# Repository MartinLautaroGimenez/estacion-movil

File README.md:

# Estación Meteorológica Móvil

Esta estación meteorológica móvil está equipada con una variedad de sensores y componentes para medir y registrar datos ambientales clave. Desde la presión atmosférica hasta la calidad del aire, esta estación proporciona información precisa para proyectos institucionales y aplicaciones diversas.

## Sensores y Componentes:

- **Módulo Sensor de Presión Atmosférica y Temperatura BMP180 (Arduino):** Proporciona lecturas precisas de la presión atmosférica y la temperatura.
- **Sensor DHT22 de Humedad y Temperatura (Arduino/Raspberry Pi):** Ofrece mediciones confiables de humedad y temperatura en tiempo real.
- **Arduino Nano Compatible ATmega328 USB C con Pines Soldados:** Controla y coordina el funcionamiento de los sensores y otros componentes.
- **Módulo Lector de Memorias Micro SD (Arduino):** Permite almacenar datos recopilados para análisis posterior.
- **Tarjeta Micro SD SanDisk Ultra 8GB Clase 10:** Proporciona capacidad de almacenamiento para registros de datos extensos.
- **BMS 2S 3A 8,4V para Baterías 18650 (2 celdas):** Protege y gestiona la carga de las baterías para una operación segura y eficiente.
- **Batería 18650 UltraFire HY18650 Cilíndrica:** Fuente de energía portátil para la estación meteorológica móvil.
- **LM2596 Fuente Step-Down DC-DC 1,23-35V 3A (Arduino):** Regula el voltaje de entrada para alimentar los componentes de manera estable.
- **Módulo Sensor de Luz Digital Ambiente BH1750 GY-302 (Arduino):** Detecta y registra niveles de luz ambiental.
- **Sensor MQ-135 de Gas (NH3, N2, CO2, Humo, etc.):** Monitoriza la calidad del aire para detectar la presencia de varios gases.

## Uso y Aplicaciones:

Esta estación meteorológica móvil es ideal para proyectos institucionales que requieren datos precisos y actualizados sobre condiciones ambientales. Puede utilizarse en una variedad de aplicaciones, incluyendo:

- Monitoreo ambiental en tiempo real.
- Investigación climática y meteorológica.
- Control de calidad del aire en entornos interiores y exteriores.
- Estudios de impacto ambiental y análisis de datos.

Con su diseño compacto y su capacidad de recopilación de datos precisa, esta estación meteorológica móvil es una herramienta valiosa para cualquier proyecto que requiera información ambiental detallada y confiable.

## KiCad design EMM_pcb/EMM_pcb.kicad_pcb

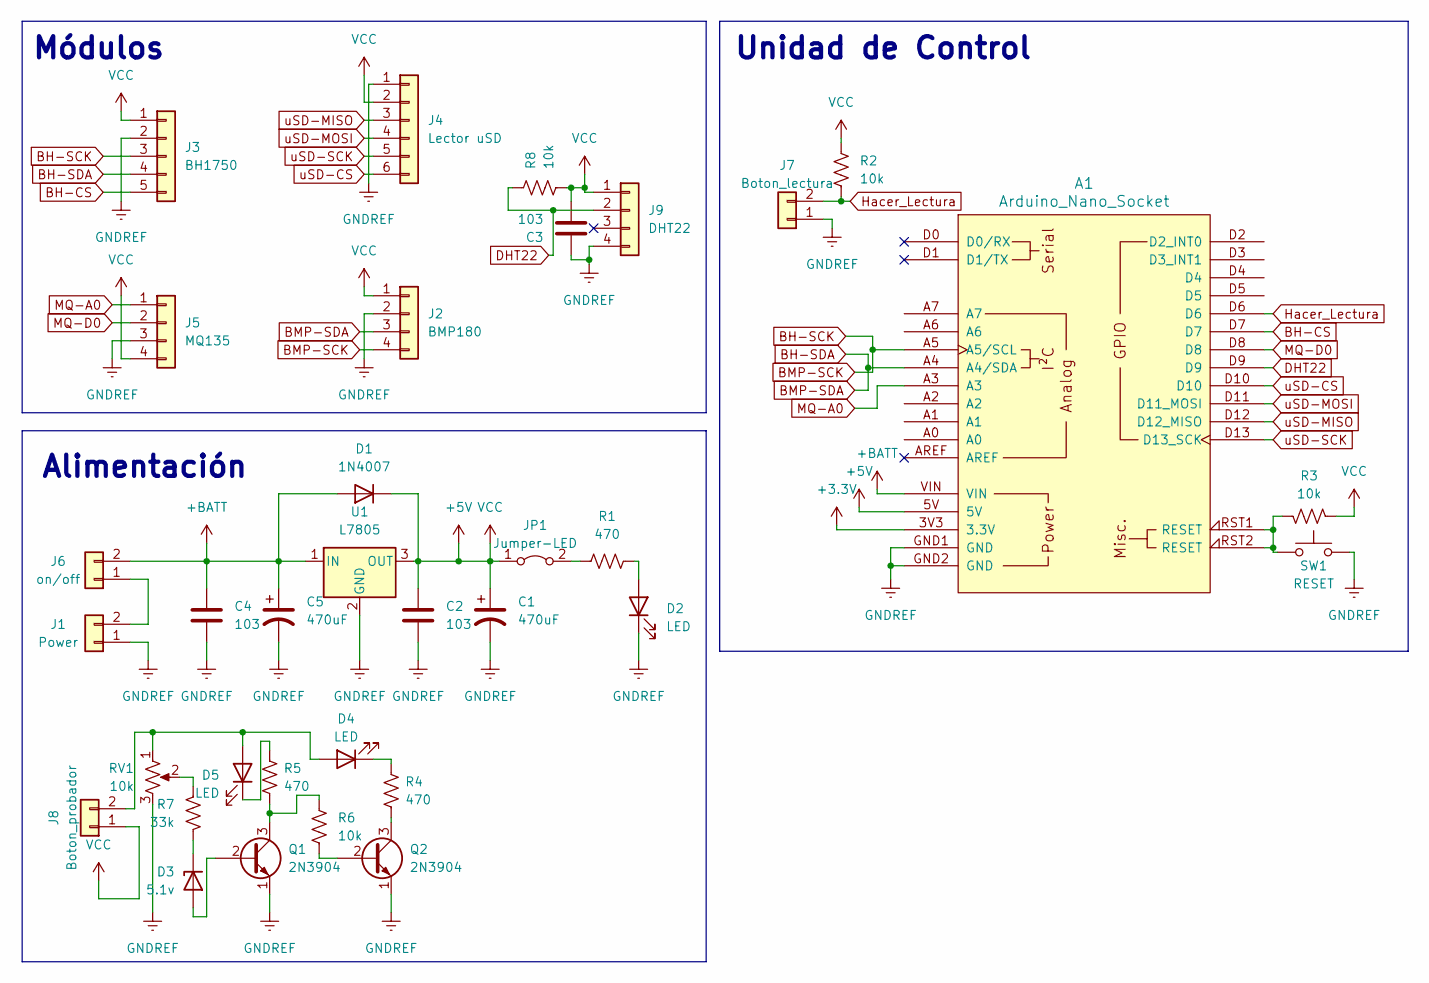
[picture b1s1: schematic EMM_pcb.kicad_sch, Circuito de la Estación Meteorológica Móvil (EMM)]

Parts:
A1: Arduino_Nano_Socket
C1, C5: 470uF; CP_Radial_D10.0mm_P5.00mm
C2, C3, C4: 103; C_Disc_D6.0mm_W2.5mm_P5.00mm
D1: 1N4007; D_DO-41_SOD81_P10.16mm_Horizontal
D2, D4, D5: LED; LED_D5.0mm
D3: 5.1v; D_DO-35_SOD27_P10.16mm_Horizontal
J1: Power; PinHeader_2x01_P2.54mm_Vertical
J2: BMP180; PinHeader_1x04_P2.54mm_Vertical
J3: BH1750; PinHeader_1x05_P2.54mm_Vertical
J4: Lector uSD; PinHeader_1x06_P2.54mm_Vertical
J5: MQ135; PinHeader_1x04_P2.54mm_Vertical
J6: on/off; PinHeader_1x02_P2.54mm_Vertical
J7: Boton_lectura; PinHeader_1x02_P2.54mm_Vertical
J8: Boton_probador; PinHeader_1x02_P2.54mm_Vertical
J9: DHT22; PinHeader_1x04_P2.54mm_Vertical
JP1: Jumper-LED; PinHeader_1x02_P2.54mm_Vertical
Q1, Q2: 2N3904; TO-92_Wide
R1, R4, R5: 470; R_Axial_DIN0207_L6.3mm_D2.5mm_P10.16mm_Horizontal
R2, R3, R6, R8: 10k; R_Axial_DIN0207_L6.3mm_D2.5mm_P10.16mm_Horizontal
R7: 33k; R_Axial_DIN0207_L6.3mm_D2.5mm_P10.16mm_Horizontal
RV1: 10k; Potentiometer_Bourns_3339P_Vertical_HandSoldering
SW1: RESET; SW_PUSH_6mm_H5mm
U1: L7805; TO-220-3_Vertical

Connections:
+3.3V: A1.3V3 (3.3V)
+5V: A1.5V, C1.1, C2.1, C3.2, D1.1 (K), J2.1, J3.1, J4.2, J5.4, J8.1, J9.1, JP1.1 (A), R2.2, R3.1, R8.1, U1.3 (OUT)
+BATT: A1.VIN, C4.1, C5.1, D1.2 (A), J6.2, U1.1 (IN)
BH-CS: A1.D7, J3.5
BH-SCK: A1.A5 (A5/SCL), J2.4, J3.3
BH-SDA: A1.A4 (A4/SDA), J2.3, J3.4
DHT22: A1.D9, J9.2, R8.2
GNDREF: A1.GND1 (GND), A1.GND2 (GND), C1.2, C2.2, C3.1, C4.2, C5.2, D2.1 (K), J1.1, J2.2, J3.2, J4.1, J5.3, J7.1, J9.4, Q1.1 (E), Q2.1 (E), RV1.3, SW1.1, U1.2 (GND)
Hacer_Lectura: A1.D6, J7.2, R2.1
MQ-A0: A1.A3, J5.1
MQ-D0: A1.D8, J5.2
unnamed: A1.RST1 (RESET), A1.RST2 (RESET), R3.2, SW1.2
unnamed: D2.2 (A), R1.2
unnamed: D3.2 (A), Q1.2 (B)
unnamed: D3.1 (K), R7.1
unnamed: D4.2 (A), D5.2 (A), J8.2, RV1.1
unnamed: D4.1 (K), R4.1
unnamed: D5.1 (K), R5.2
unnamed: J1.2, J6.1
unnamed: JP1.2 (B), R1.1
unnamed: Q1.3 (C), R5.1, R6.2
unnamed: Q2.2 (B), R6.1
unnamed: Q2.3 (C), R4.2
unnamed: R7.2, RV1.2
uSD-CS: A1.D10, J4.6
uSD-MISO: A1.D12 (D12_MISO), J4.3
uSD-MOSI: A1.D11 (D11_MOSI), J4.4
uSD-SCK: A1.D13 (D13_SCK), J4.5

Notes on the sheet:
Alimentación
Unidad de Control
Módulos

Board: 2 copper layers, 34 parts (0 on the bottom side), 27 nets, no tracks yet.

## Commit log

2024-02-24 Primer Commit
2024-02-24 Se ha creado proyecto de KiCad y carpetas para ordenar
2024-02-24 agregado de README.md en las carpetas raíces
2024-02-24 Se añadio el diagrama de flujo, se actualizo el readme, se creo el .ino y se añadio un ejemplo de conexion mqtt en python
2024-02-25 Se avanzó con el diagrama electrónico de la PCB
2024-02-26 Se añadieron pruebas de los modulos mq6 y sd. Se modifico el orden de la pcb Se a Co-authored-by: Mario Papetti <Mario-dango@users.noreply.github.com>
